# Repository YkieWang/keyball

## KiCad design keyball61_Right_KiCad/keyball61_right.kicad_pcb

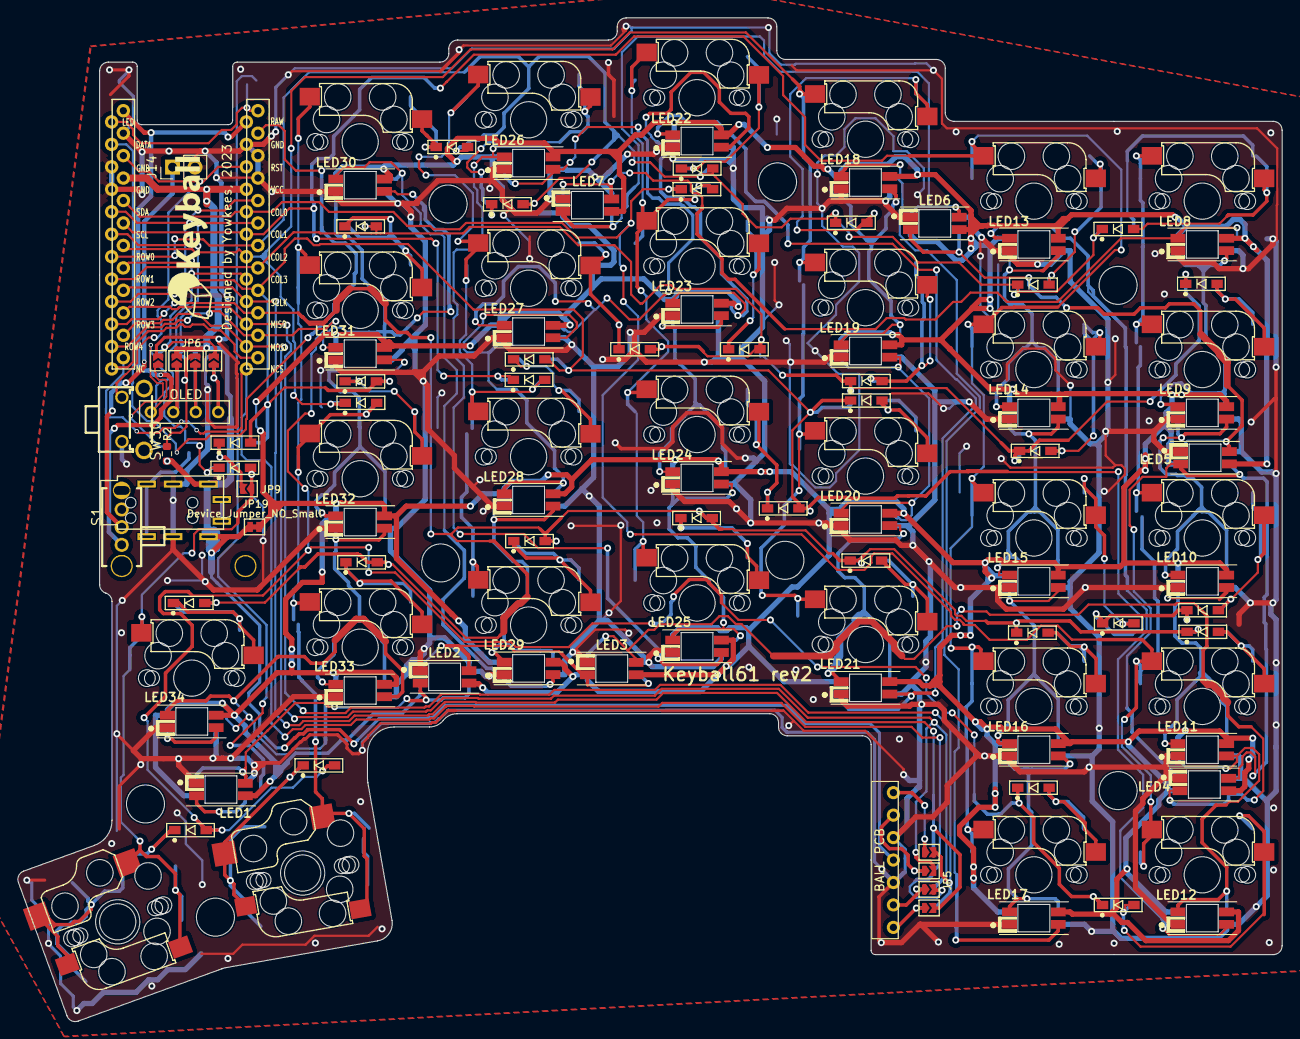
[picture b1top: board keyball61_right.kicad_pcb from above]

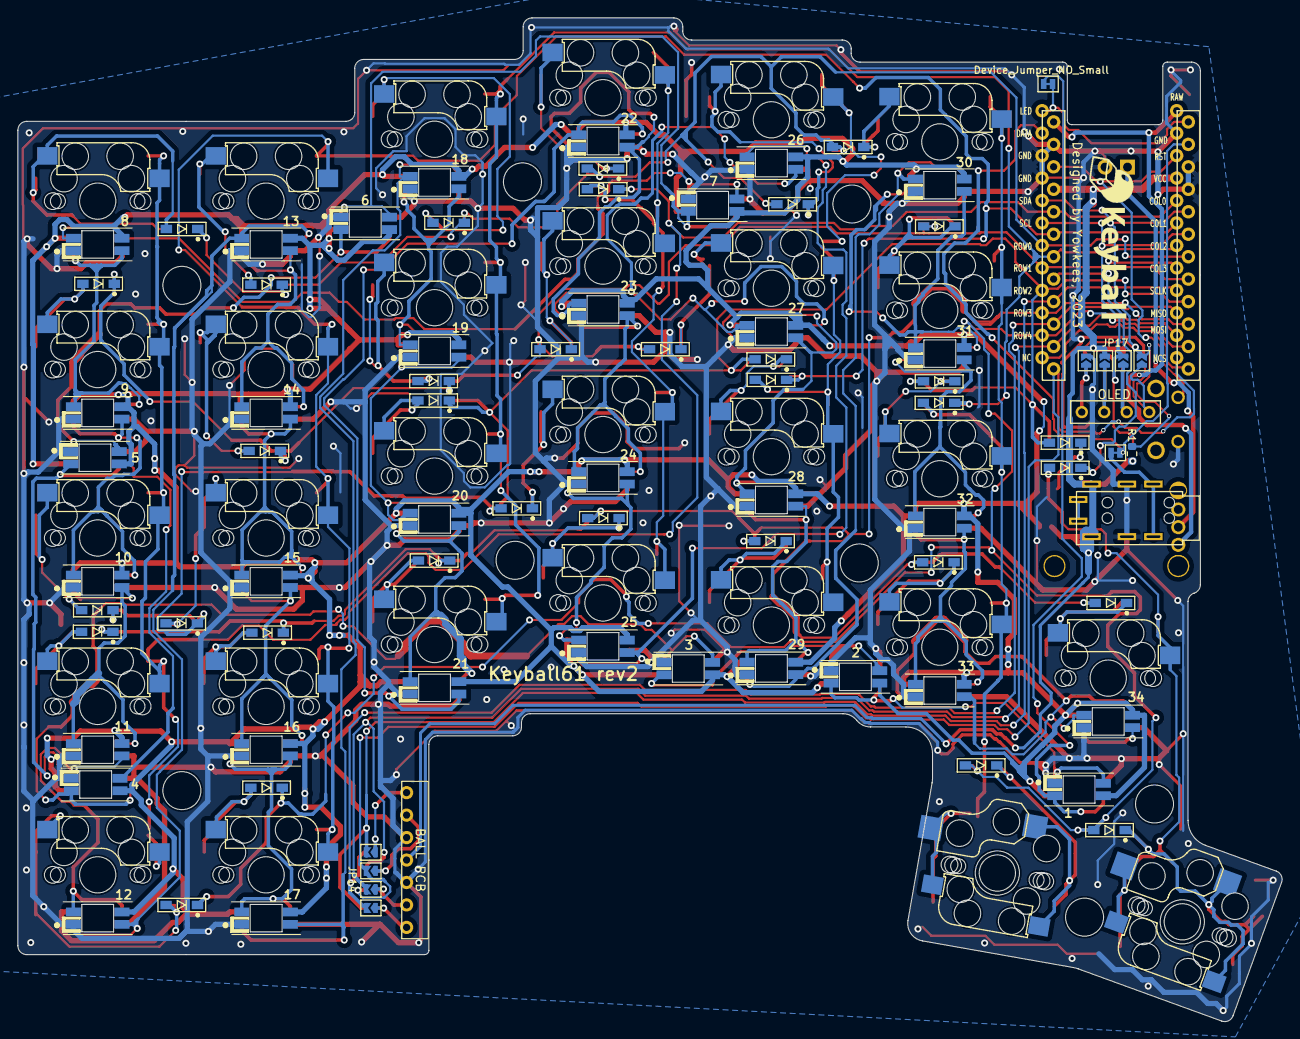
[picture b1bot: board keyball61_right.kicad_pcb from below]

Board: 2 copper layers, 142.9 x 113.5 mm, 136 parts (11 on the bottom side), 71 nets.

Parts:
D1, D2, D3, D4, D5, D6, D7, D8, D9, D10, D11, D12, D13, D14, D15, D16, D17, D18, D19, D20, D21, D22, D23, D24, D25, D26, D27, D28, D29, D30, D31, D32, D33, D34: D; D3_SMD_v2_BOTH
J1: OLED
J2: BALL_PCB; Mac8_L_7pin_contact_NEW2023
J3, J4: Conn_01x01-Connector_Generic; MountingHole_2.2mm_M2_Pad
J5, J6, J7, J8, J9, J10, J11, J12: Conn_01x01-Connector_Generic; MountingHole_4.3mm_M4
J13: TRS_JACK; TRRS_JACK_MJ4PP9
J14: Conn_01x02_Socket; PinHeader_1x02_P2.54mm_Vertical
JP1, JP2, JP3, JP4, JP5, JP6, JP7, JP8, JP9, JP10, JP11, JP12, JP13, JP14, JP15, JP16, JP17: Device_Jumper_NO_Small; Jumper_NEW
JP18: Device_Jumper; JP025
JP19: Device_Jumper_NO_Small; JP06
JP20: Device_Jumper_NO_Small; JP025
LED1, LED2, LED3, LED4, LED5, LED6, LED7: YS-SK6812MINI-E; YS-SK6812MINI-Keyball-BL
LED8, LED9, LED10, LED11, LED12, LED13, LED14, LED15, LED16, LED17, LED18, LED19, LED20, LED21, LED22, LED23, LED24, LED25, LED26, LED27, LED28, LED29, LED30, LED31, LED32, LED33, LED34: YS-SK6812MINI-E; YS-SK6812MINI-Keyball-TL
R1, R2: PULL_UP; R_0603_1608Metric
S1: SW-TH_SK12D07VG5
SW1, SW2, SW3, SW4, SW5, SW6, SW7, SW8, SW9, SW10, SW11, SW12, SW13, SW14, SW15, SW16, SW17, SW18, SW19, SW20, SW21, SW22, SW23, SW24, SW25, SW26, SW27: SW_PUSH-kbd; CherryMX_MidHeight_Hotswap
SW28, SW29: SW_PUSH-kbd; MX&Choc_V1_V2_Hotswap_BOTH
SW30: RESET_SW; KEY-TH_TC-3601-5-100G
U1: ProMicro-kbd; ProMicro_v2_for61

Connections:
BATT: S1.1, U1.24 (RAW)
COL0: D31.1 (K), SW1.1, SW7.1, SW13.1, SW19.1, SW26.1, U1.20 (F4)
COL1: D32.1 (K), SW2.1, SW8.1, SW14.1, SW20.1, SW27.1, U1.19 (F5)
COL2: D33.1 (K), SW3.1, SW9.1, SW15.1, SW21.1, U1.18 (F6)
COL3: D34.1 (K), U1.17 (F7)
DATA: JP18.2, U1.2 (RX)
GND: J2.3, J2.5, J13.C, J14.2, JP2.2, JP17.2, LED1.3 (GND), LED2.3 (GND), LED3.3 (GND), LED4.3 (GND), LED5.3 (GND), LED6.3 (GND), LED7.3 (GND), LED8.3 (GND), LED9.3 (GND), LED10.3 (GND), LED11.3 (GND), LED12.3 (GND), LED13.3 (GND), LED14.3 (GND), LED15.3 (GND), LED16.3 (GND), LED17.3 (GND), LED18.3 (GND), LED19.3 (GND), LED20.3 (GND), LED21.3 (GND), LED22.3 (GND), LED23.3 (GND), LED24.3 (GND), LED25.3 (GND), LED26.3 (GND), LED27.3 (GND), LED28.3 (GND), LED29.3 (GND), LED30.3 (GND), LED31.3 (GND), LED32.3 (GND), LED33.3 (GND), LED34.3 (GND), SW30.2, U1.3 (GND), U1.4 (GND), U1.23 (GND)
LED: JP20.1, U1.1 (TX)
MISO: JP1.2, JP16.2, U1.15 (B3)
MOSI: JP3.2, JP14.2, U1.14 (B2)
NCS: JP5.2, JP12.2, U1.13 (B6)
unnamed: D30.1 (K), JP9.2
unnamed: D31.2 (A), SW4.1, SW10.1, SW16.1, SW22.1
unnamed: D32.2 (A), SW5.1, SW11.1, SW17.1, SW23.1
unnamed: D33.2 (A), SW6.1, SW12.1, SW18.1, SW24.1, SW28.1
unnamed: D34.2 (A), JP9.1, SW25.1, SW29.1
unnamed: J1.1, JP2.1, JP11.1
unnamed: J1.2, JP4.1, JP13.1
unnamed: J1.3, JP6.1, JP15.1
unnamed: J1.4, JP8.1, JP17.1
unnamed: J2.1, JP1.1, JP10.1
unnamed: J2.2, JP3.1, JP12.1
unnamed: J2.6, JP5.1, JP14.1
unnamed: J2.7, JP7.1, JP16.1
unnamed: J14.1, S1.2
unnamed: JP20.2, LED1.4 (DIN)
unnamed: LED1.2 (DOUT), LED2.4 (DIN)
unnamed: JP19.1, LED1.1 (VDD), LED2.1 (VDD), LED3.1 (VDD), LED4.1 (VDD), LED5.1 (VDD), LED6.1 (VDD), LED7.1 (VDD), LED8.1 (VDD), LED9.1 (VDD), LED10.1 (VDD), LED11.1 (VDD), LED12.1 (VDD), LED13.1 (VDD), LED14.1 (VDD), LED15.1 (VDD), LED16.1 (VDD), LED17.1 (VDD), LED18.1 (VDD), LED19.1 (VDD), LED20.1 (VDD), LED21.1 (VDD), LED22.1 (VDD), LED23.1 (VDD), LED24.1 (VDD), LED25.1 (VDD), LED26.1 (VDD), LED27.1 (VDD), LED28.1 (VDD), LED29.1 (VDD), LED30.1 (VDD), LED31.1 (VDD), LED32.1 (VDD), LED33.1 (VDD), LED34.1 (VDD)
unnamed: LED2.2 (DOUT), LED3.4 (DIN)
unnamed: LED3.2 (DOUT), LED4.4 (DIN)
unnamed: LED4.2 (DOUT), LED5.4 (DIN)
unnamed: LED5.2 (DOUT), LED6.4 (DIN)
unnamed: LED6.2 (DOUT), LED7.4 (DIN)
unnamed: LED7.2 (DOUT), LED8.4 (DIN)
unnamed: LED8.2 (DOUT), LED9.4 (DIN)
unnamed: LED9.2 (DOUT), LED10.4 (DIN)
unnamed: LED10.2 (DOUT), LED11.4 (DIN)
unnamed: LED11.2 (DOUT), LED12.4 (DIN)
unnamed: LED12.2 (DOUT), LED13.4 (DIN)
unnamed: LED13.2 (DOUT), LED14.4 (DIN)
unnamed: LED14.2 (DOUT), LED15.4 (DIN)
unnamed: LED15.2 (DOUT), LED16.4 (DIN)
unnamed: LED16.2 (DOUT), LED17.4 (DIN)
unnamed: LED17.2 (DOUT), LED18.4 (DIN)
unnamed: LED18.2 (DOUT), LED19.4 (DIN)
unnamed: LED19.2 (DOUT), LED20.4 (DIN)
unnamed: LED20.2 (DOUT), LED21.4 (DIN)
unnamed: LED21.2 (DOUT), LED22.4 (DIN)
unnamed: LED22.2 (DOUT), LED23.4 (DIN)
unnamed: LED23.2 (DOUT), LED24.4 (DIN)
unnamed: LED24.2 (DOUT), LED25.4 (DIN)
unnamed: LED25.2 (DOUT), LED26.4 (DIN)
unnamed: LED26.2 (DOUT), LED27.4 (DIN)
unnamed: LED27.2 (DOUT), LED28.4 (DIN)
unnamed: LED28.2 (DOUT), LED29.4 (DIN)
unnamed: LED29.2 (DOUT), LED30.4 (DIN)
unnamed: LED30.2 (DOUT), LED31.4 (DIN)
unnamed: LED31.2 (DOUT), LED32.4 (DIN)
unnamed: LED32.2 (DOUT), LED33.4 (DIN)
unnamed: LED33.2 (DOUT), LED34.4 (DIN)
unnamed: J13.B, JP18.1
RESET: SW30.1, U1.22 (RST)
ROW0: D1.1 (K), D2.1 (K), D3.1 (K), D4.2 (A), D5.2 (A), D6.2 (A), U1.7 (D4)
ROW1: D7.1 (K), D8.1 (K), D9.1 (K), D10.2 (A), D11.2 (A), D12.2 (A), U1.8 (C6)
ROW2: D13.1 (K), D14.1 (K), D15.1 (K), D16.2 (A), D17.2 (A), D18.2 (A), D30.2 (A), U1.9 (D7)
ROW3: D19.1 (K), D20.1 (K), D21.1 (K), D22.2 (A), D23.2 (A), D24.2 (A), D25.2 (A), U1.10 (E6)
ROW4: D26.1 (K), D27.1 (K), D28.2 (A), D29.2 (A), U1.11 (B4)
SCL: JP6.2, JP13.2, R2.2, U1.6 (SCL)
SCLK: JP7.2, JP10.2, U1.16 (B1)
SDA: JP8.2, JP11.2, R1.2, U1.5 (SDA)
VCC: J2.4, J13.D, JP4.2, JP15.2, JP19.2, R1.1, R2.1, U1.21 (VCC)

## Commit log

2024-11-24 init
